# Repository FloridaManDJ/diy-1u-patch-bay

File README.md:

# diy-1u-patch-bay
1U 1/4" audio patch bay

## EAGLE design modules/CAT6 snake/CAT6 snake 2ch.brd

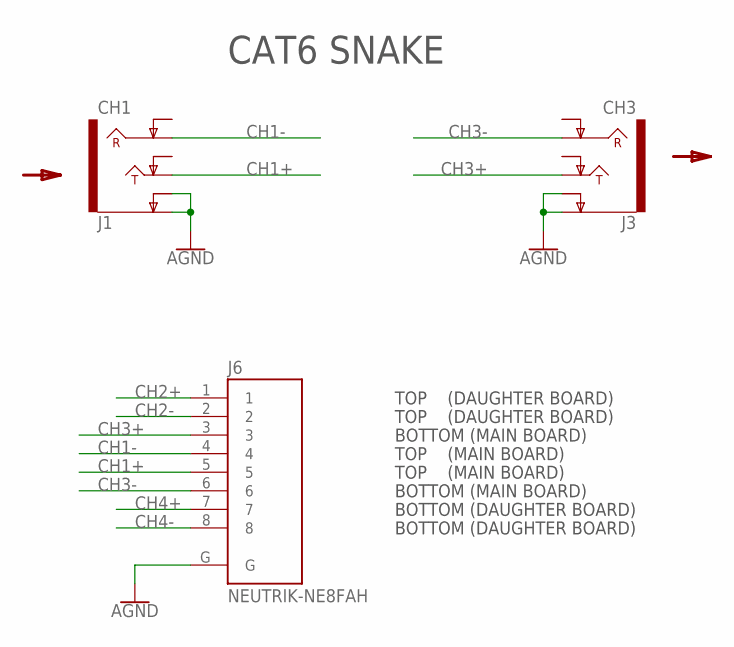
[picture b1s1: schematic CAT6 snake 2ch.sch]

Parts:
J1: CH1; NEUTRIK-NRJ6HF
J3: CH3; NEUTRIK-NRJ6HF
J6: NEUTRIK-NE8FAH; NEUTRIK_NE8FAH

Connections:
AGND: J1.S (EARTH), J1.SN (EARTH-NORM), J3.S (EARTH), J3.SN (EARTH-NORM), J6.G
CH1+: J1.T (TIP), J6.5
CH1-: J1.R (RING), J6.4
CH2+: J6.1
CH2-: J6.2
CH3+: J3.T (TIP), J6.3
CH3-: J3.R (RING), J6.6
CH4+: J6.7
CH4-: J6.8

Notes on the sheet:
TOP (MAIN BOARD)
TOP (DAUGHTER BOARD)
BOTTOM (DAUGHTER BOARD)
BOTTOM (MAIN BOARD)
CAT6 SNAKE

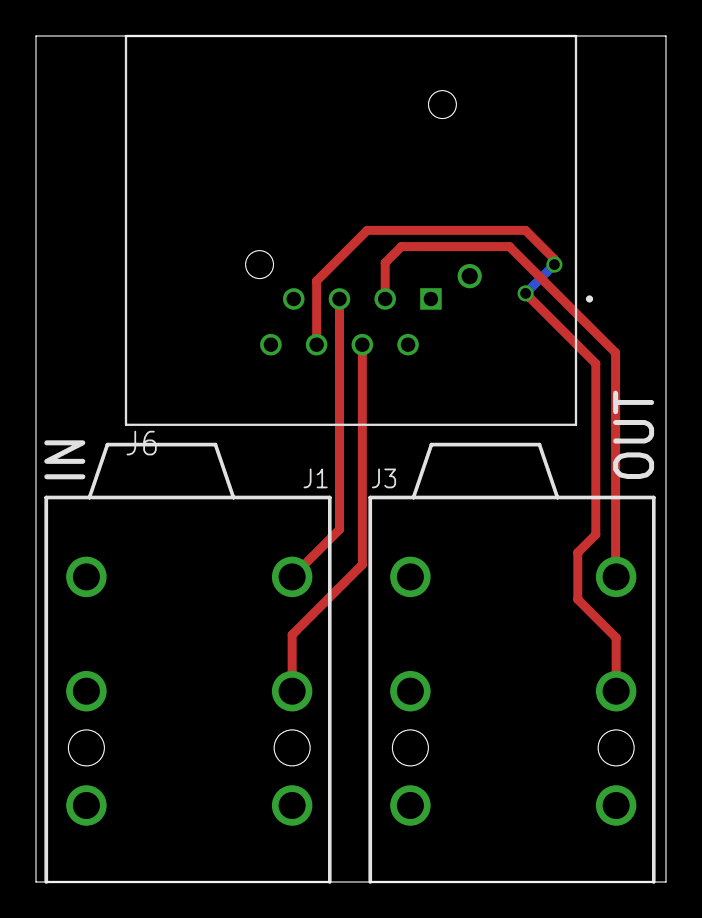
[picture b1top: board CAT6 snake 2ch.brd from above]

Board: 2 copper layers, 35.0 x 47.0 mm, 3 parts (0 on the bottom side), 5 nets.

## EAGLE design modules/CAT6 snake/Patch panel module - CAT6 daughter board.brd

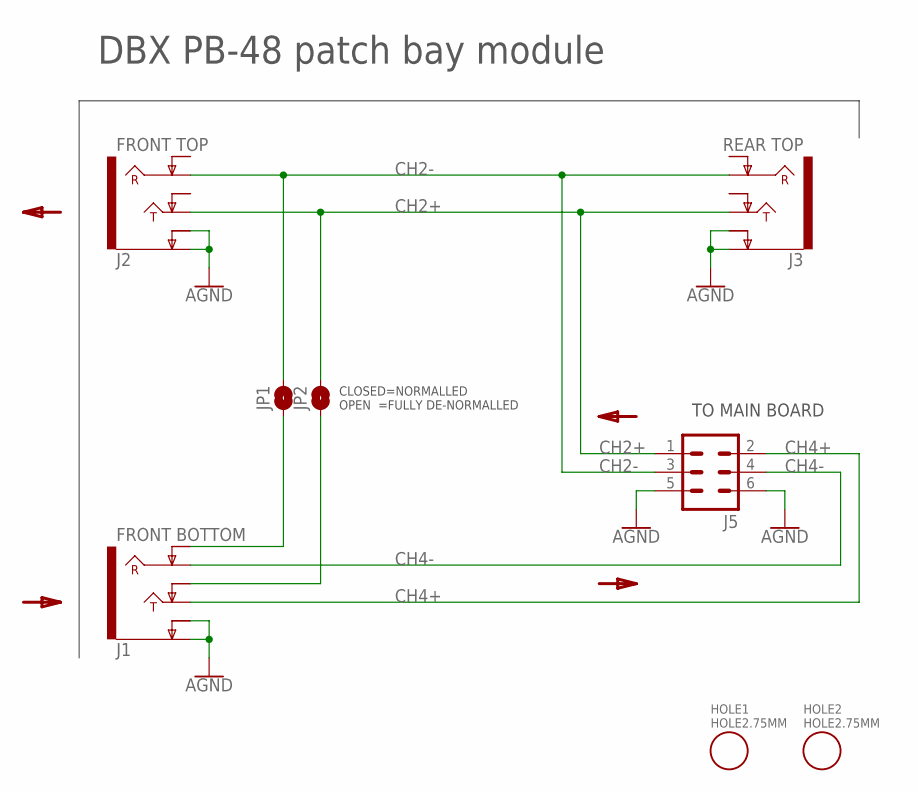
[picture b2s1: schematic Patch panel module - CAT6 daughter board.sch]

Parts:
HOLE1, HOLE2: HOLE2.75MM; HOLE-2.75MM
J1: FRONT BOTTOM; NEUTRIK-NRJ6HF
J2: FRONT TOP; NEUTRIK-NRJ6HF
J3: REAR TOP; NEUTRIK-NRJ6HF
J5: MA03-2
JP1, JP2: JUMPER-SMT_2_NO_NO-SILK_ROUND; SMT-JUMPER_2_NO_NO-SILK_ROUND

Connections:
AGND: J1.S (EARTH), J1.SN (EARTH-NORM), J2.S (EARTH), J2.SN (EARTH-NORM), J3.S (EARTH), J3.SN (EARTH-NORM), J5.5, J5.6
CH2+: J2.T (TIP), J3.T (TIP), J5.1, JP2.2
CH2-: J2.R (RING), J3.R (RING), J5.3, JP1.2
CH4+: J1.T (TIP), J5.2
CH4-: J1.R (RING), J5.4
unnamed: J1.RN (RING-NORM), JP1.1
unnamed: J1.TN (TIP-NORM), JP2.1

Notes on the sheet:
TO MAIN BOARD
CLOSED=NORMALLED OPEN =FULLY DE-NORMALLED
DBX PB-48 patch bay module

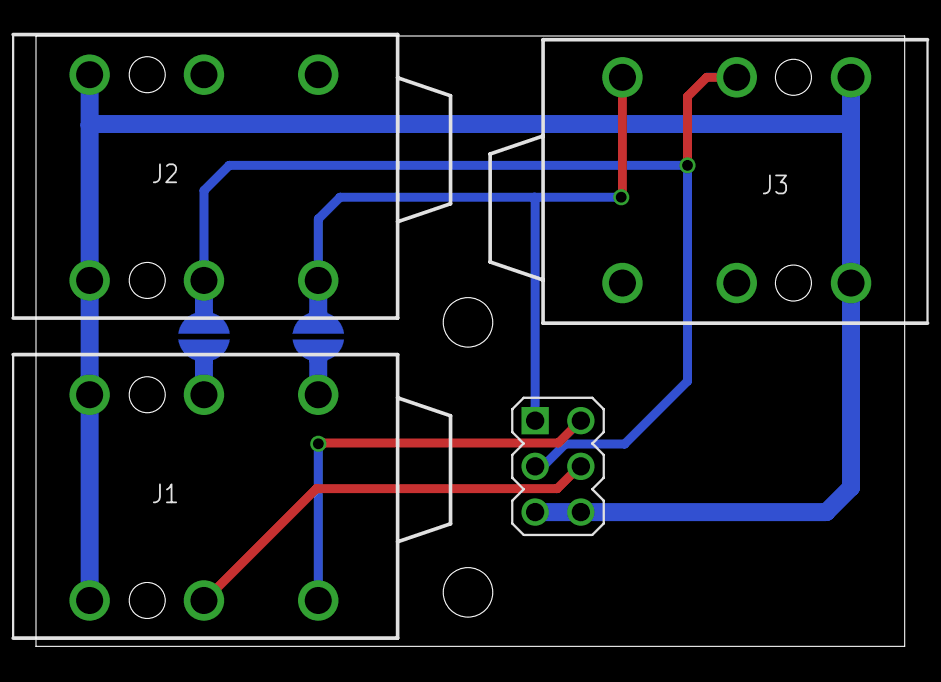
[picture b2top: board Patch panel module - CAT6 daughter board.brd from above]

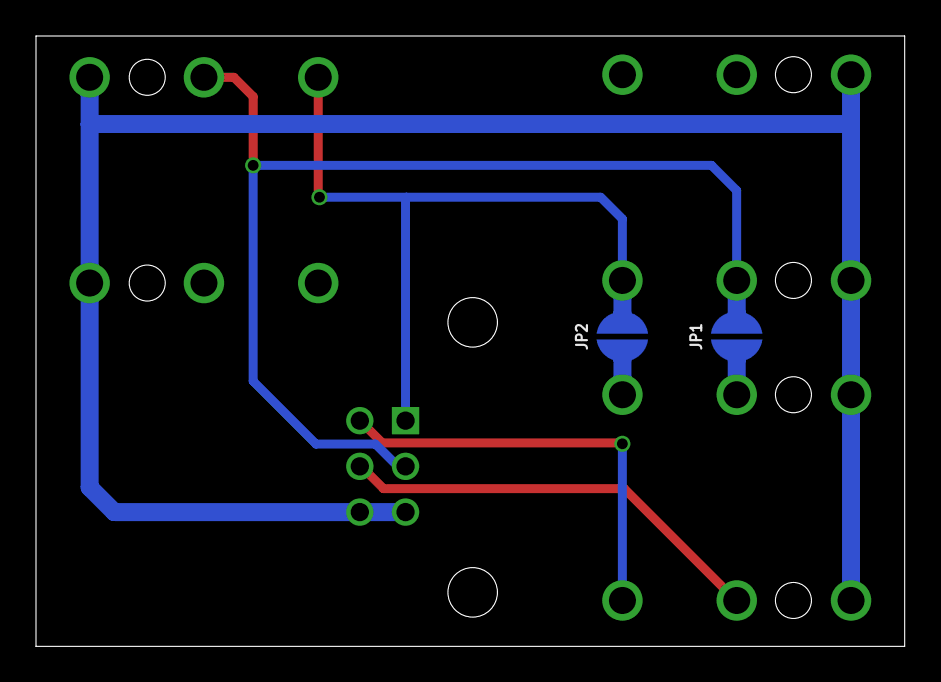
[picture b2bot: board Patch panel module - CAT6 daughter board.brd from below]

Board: 2 copper layers, 48.3 x 33.9 mm, 8 parts (2 on the bottom side), 7 nets.

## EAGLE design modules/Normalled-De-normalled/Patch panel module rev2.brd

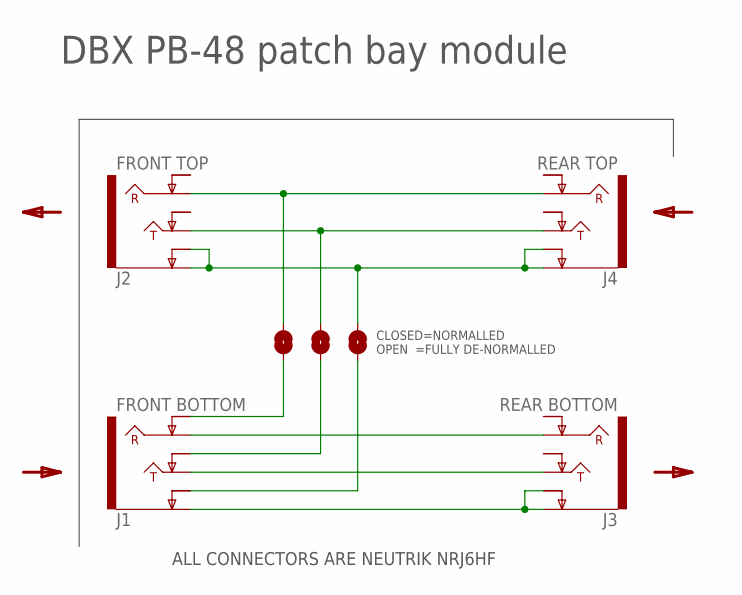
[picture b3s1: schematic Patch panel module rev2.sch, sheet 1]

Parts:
J1: FRONT BOTTOM; NEUTRIK-NRJ6HF
J2: FRONT TOP; NEUTRIK-NRJ6HF
J3: REAR BOTTOM; NEUTRIK-NRJ6HF
J4: REAR TOP; NEUTRIK-NRJ6HF
JP1, JP2, JP3: JUMPER-SMT_2_NO_NO-SILK_ROUND; SMT-JUMPER_2_NO_NO-SILK_ROUND

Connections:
unnamed: J2.S (EARTH), J2.SN (EARTH-NORM), J4.S (EARTH), J4.SN (EARTH-NORM), JP1.1
unnamed: J2.R (RING), J4.R (RING), JP3.1
unnamed: J2.T (TIP), J4.T (TIP), JP2.1
unnamed: J1.R (RING), J3.R (RING)
unnamed: J1.T (TIP), J3.T (TIP)
unnamed: J1.S (EARTH), J3.S (EARTH), J3.SN (EARTH-NORM)
unnamed: J1.SN (EARTH-NORM), JP1.2
unnamed: J1.TN (TIP-NORM), JP2.2
unnamed: J1.RN (RING-NORM), JP3.2

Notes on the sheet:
DBX PB-48 patch bay module
ALL CONNECTORS ARE NEUTRIK NRJ6HF
CLOSED=NORMALLED OPEN =FULLY DE-NORMALLED

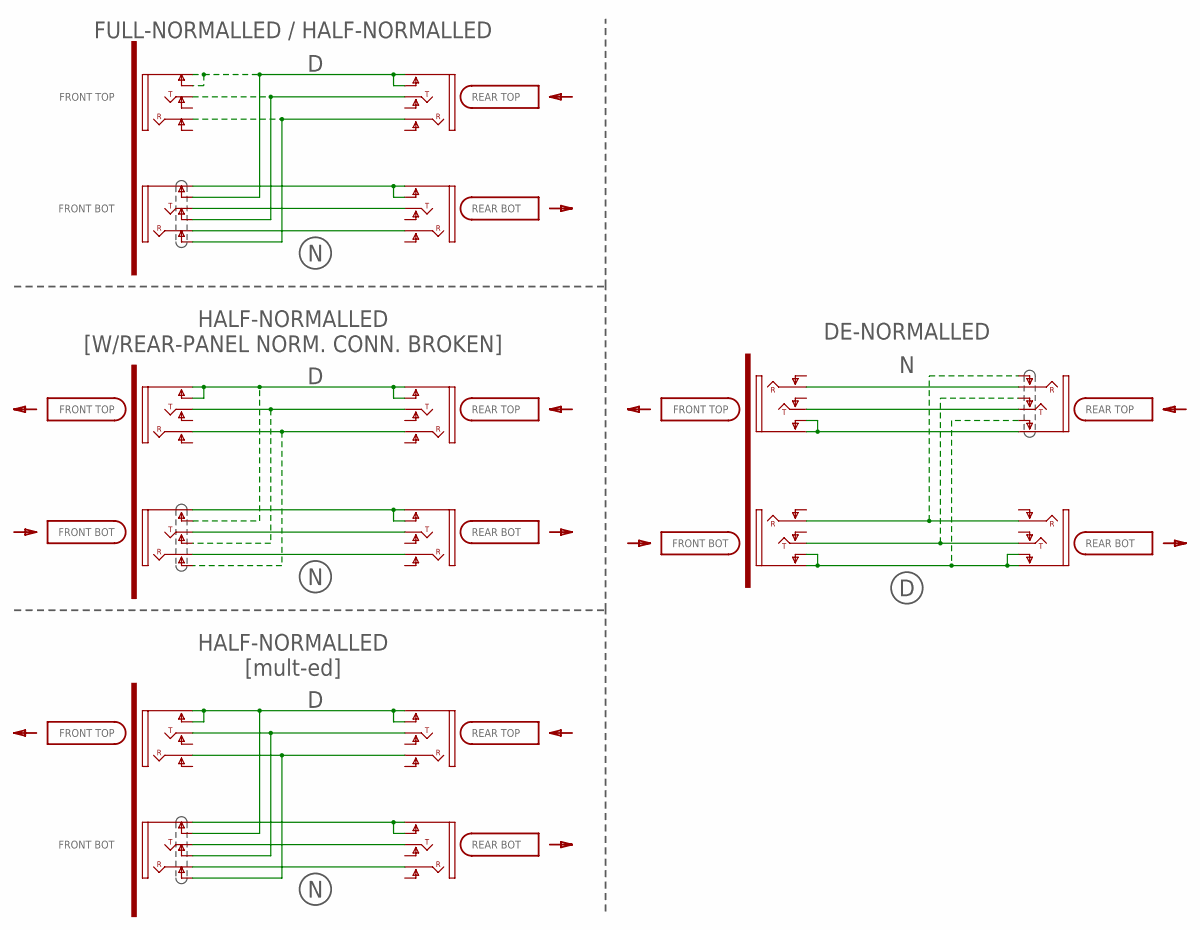
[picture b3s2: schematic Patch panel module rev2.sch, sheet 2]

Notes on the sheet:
FRONT TOP
FRONT BOT
REAR TOP
REAR BOT
FULL-NORMALLED / HALF-NORMALLED
HALF-NORMALLED [W/REAR-PANEL NORM. CONN. BROKEN]
HALF-NORMALLED [mult-ed]
DE-NORMALLED

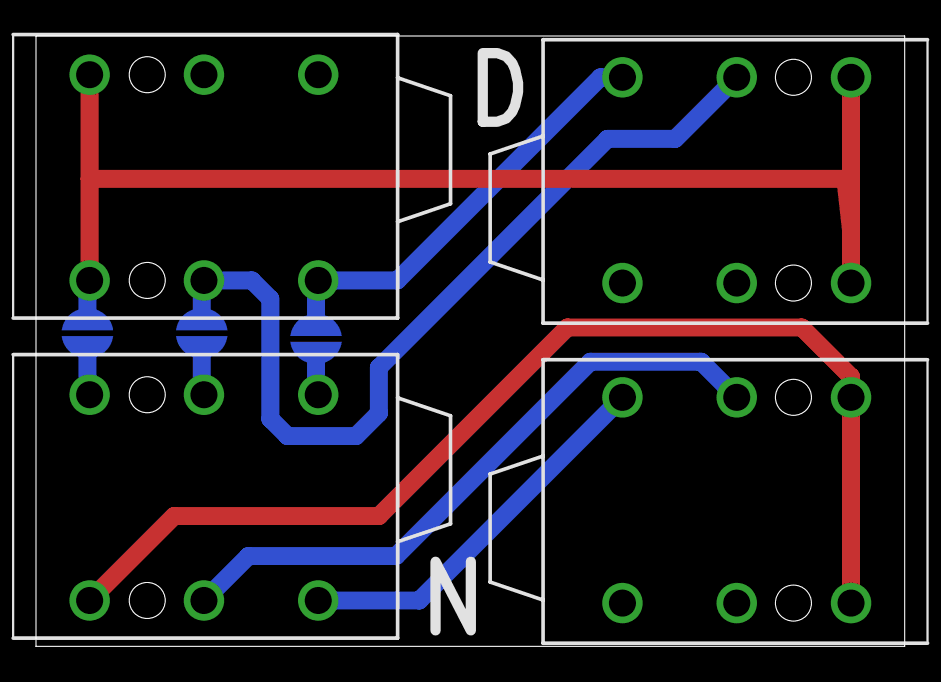
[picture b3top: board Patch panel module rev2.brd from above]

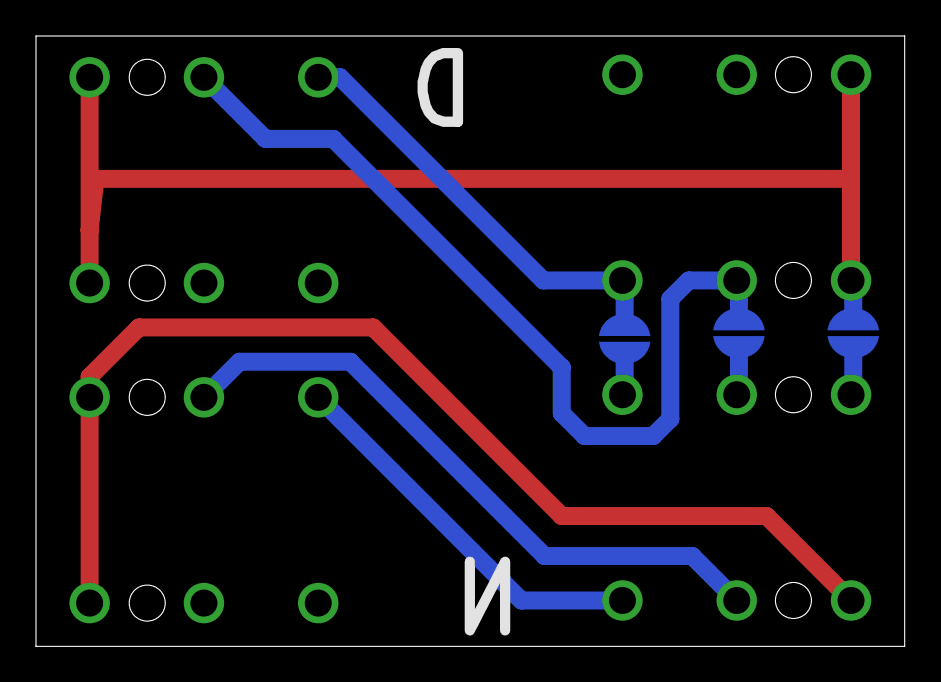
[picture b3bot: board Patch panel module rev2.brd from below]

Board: 2 copper layers, 48.3 x 33.9 mm, 7 parts (3 on the bottom side), 9 nets.

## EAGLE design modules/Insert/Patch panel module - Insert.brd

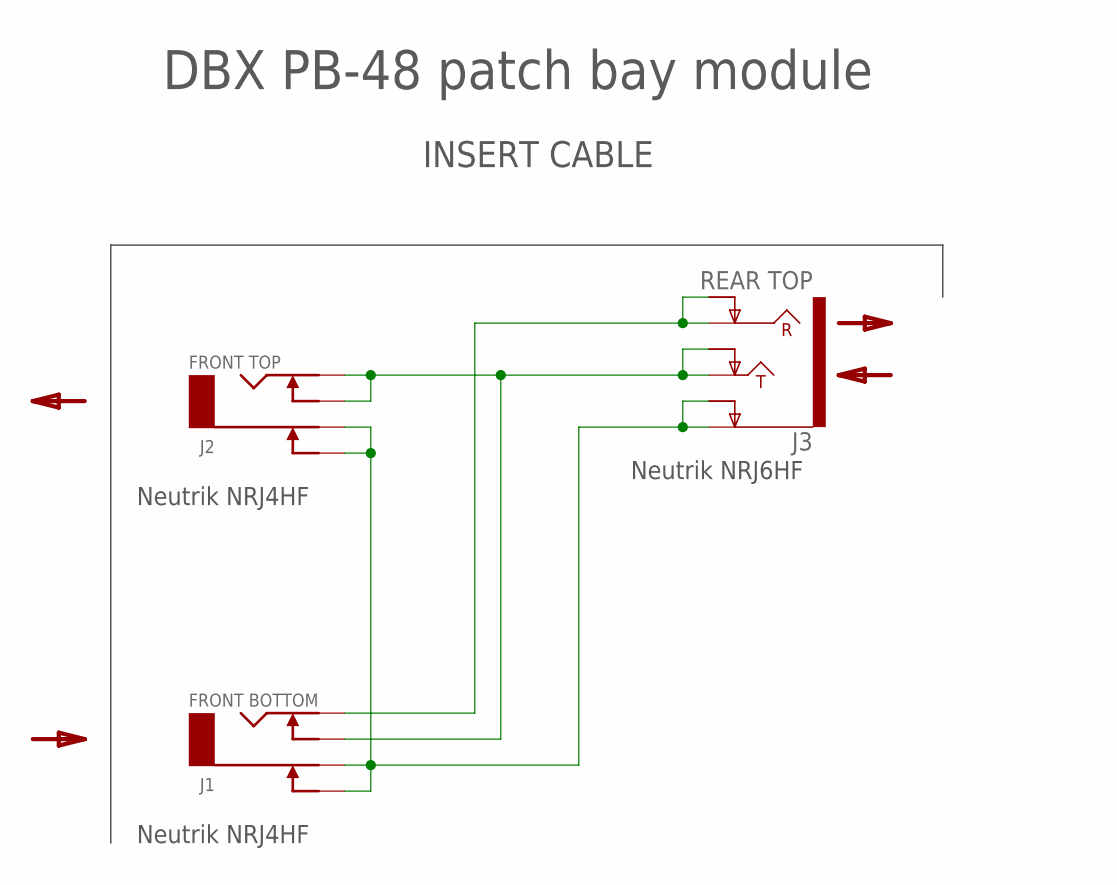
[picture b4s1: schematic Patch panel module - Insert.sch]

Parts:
J1: FRONT BOTTOM; NEUTRIK-NRJ4HF
J2: FRONT TOP; NEUTRIK-NRJ4HF
J3: REAR TOP; NEUTRIK-NRJ6HF

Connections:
unnamed: J1.TN, J2.T (TIP), J2.TN, J3.T (TIP), J3.TN (TIP-NORM)
unnamed: J1.T (TIP), J3.R (RING), J3.RN (RING-NORM)
unnamed: J1.S (SLEEVE), J1.SN, J2.S (SLEEVE), J2.SN, J3.S (EARTH), J3.SN (EARTH-NORM)

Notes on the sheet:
DBX PB-48 patch bay module
Neutrik NRJ6HF
Neutrik NRJ4HF
INSERT CABLE

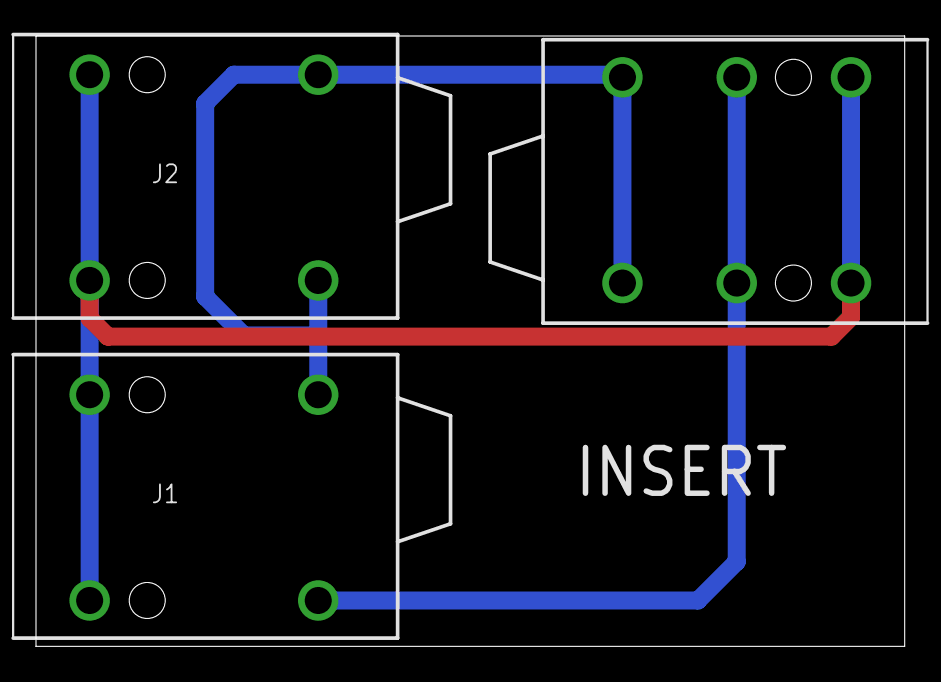
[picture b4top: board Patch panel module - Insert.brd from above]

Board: 2 copper layers, 48.3 x 33.9 mm, 3 parts (0 on the bottom side), 3 nets.

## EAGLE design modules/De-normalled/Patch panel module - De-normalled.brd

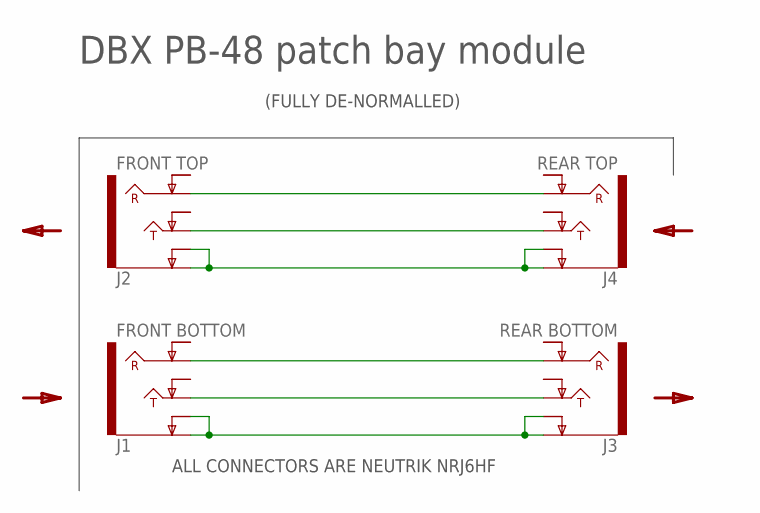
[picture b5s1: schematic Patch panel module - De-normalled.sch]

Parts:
J1: FRONT BOTTOM; NEUTRIK-NRJ6HF
J2: FRONT TOP; NEUTRIK-NRJ6HF
J3: REAR BOTTOM; NEUTRIK-NRJ6HF
J4: REAR TOP; NEUTRIK-NRJ6HF

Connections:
unnamed: J2.S (EARTH), J2.SN (EARTH-NORM), J4.S (EARTH), J4.SN (EARTH-NORM)
unnamed: J2.R (RING), J4.R (RING)
unnamed: J2.T (TIP), J4.T (TIP)
unnamed: J1.R (RING), J3.R (RING)
unnamed: J1.T (TIP), J3.T (TIP)
unnamed: J1.S (EARTH), J1.SN (EARTH-NORM), J3.S (EARTH), J3.SN (EARTH-NORM)

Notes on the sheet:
DBX PB-48 patch bay module
(FULLY DE-NORMALLED)
ALL CONNECTORS ARE NEUTRIK NRJ6HF

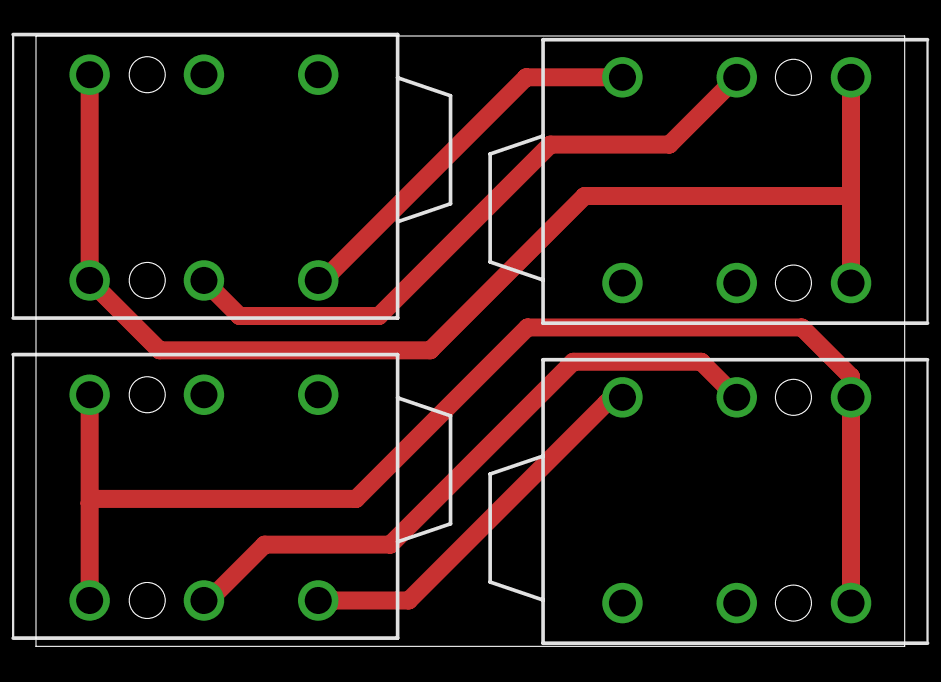
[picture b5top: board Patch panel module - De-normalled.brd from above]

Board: 2 copper layers, 48.3 x 33.9 mm, 4 parts (0 on the bottom side), 6 nets.

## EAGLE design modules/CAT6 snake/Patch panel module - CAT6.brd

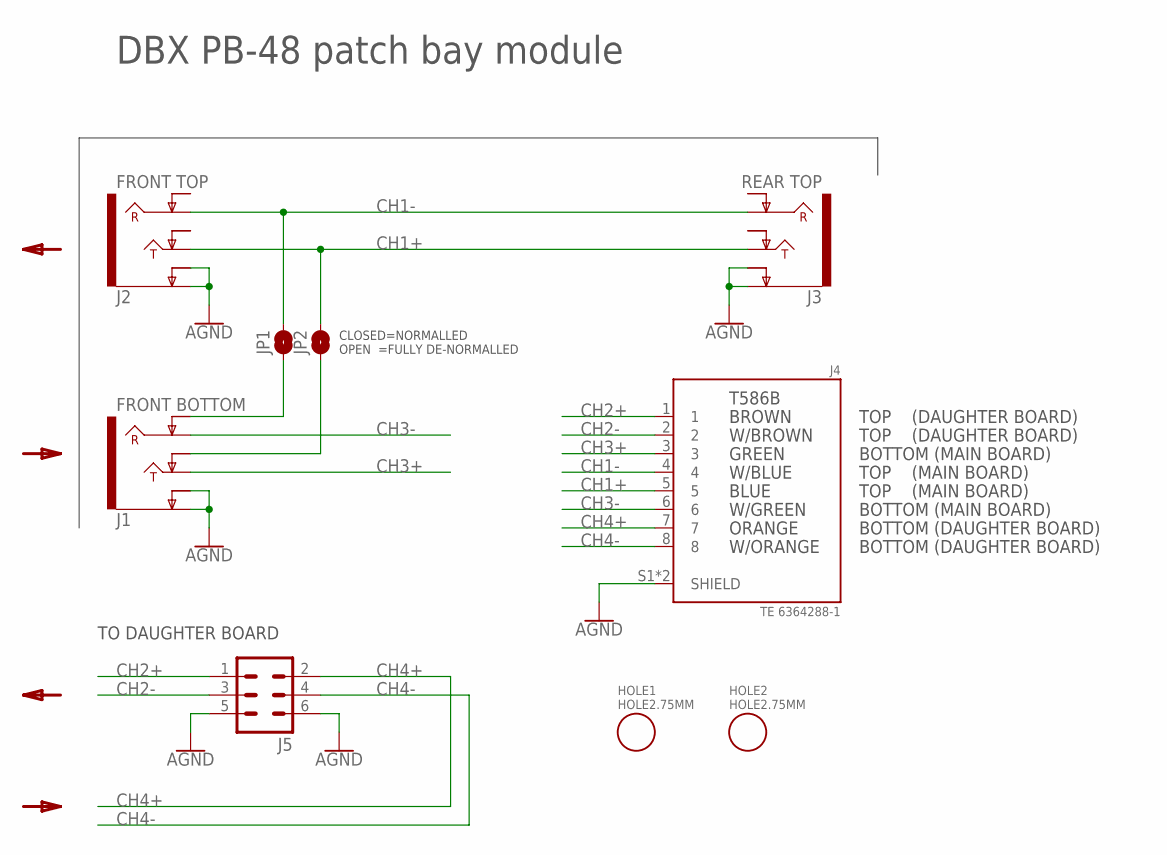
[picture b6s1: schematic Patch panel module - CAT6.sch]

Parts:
HOLE1, HOLE2: HOLE2.75MM; HOLE-2.75MM
J1: FRONT BOTTOM; NEUTRIK-NRJ6HF
J2: FRONT TOP; NEUTRIK-NRJ6HF
J3: REAR TOP; NEUTRIK-NRJ6HF
J4: TE 6364288-1; RJ45-TE-6364288-1
J5: MA03-2
JP1, JP2: JUMPER-SMT_2_NO_NO-SILK_ROUND; SMT-JUMPER_2_NO_NO-SILK_ROUND

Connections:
AGND: J1.S (EARTH), J1.SN (EARTH-NORM), J2.S (EARTH), J2.SN (EARTH-NORM), J3.S (EARTH), J3.SN (EARTH-NORM), J4.S1 (SHIELD), J4.S2 (SHIELD), J5.5, J5.6
CH1+: J2.T (TIP), J3.T (TIP), J4.5, JP2.2
CH1-: J2.R (RING), J3.R (RING), J4.4, JP1.2
CH2+: J4.1, J5.1
CH2-: J4.2, J5.3
CH3+: J1.T (TIP), J4.3
CH3-: J1.R (RING), J4.6
CH4+: J4.7, J5.2
CH4-: J4.8, J5.4
unnamed: J1.RN (RING-NORM), JP1.1
unnamed: J1.TN (TIP-NORM), JP2.1

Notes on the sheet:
TO DAUGHTER BOARD
TOP (MAIN BOARD)
TOP (DAUGHTER BOARD)
BOTTOM (DAUGHTER BOARD)
BOTTOM (MAIN BOARD)
CLOSED=NORMALLED OPEN =FULLY DE-NORMALLED
DBX PB-48 patch bay module

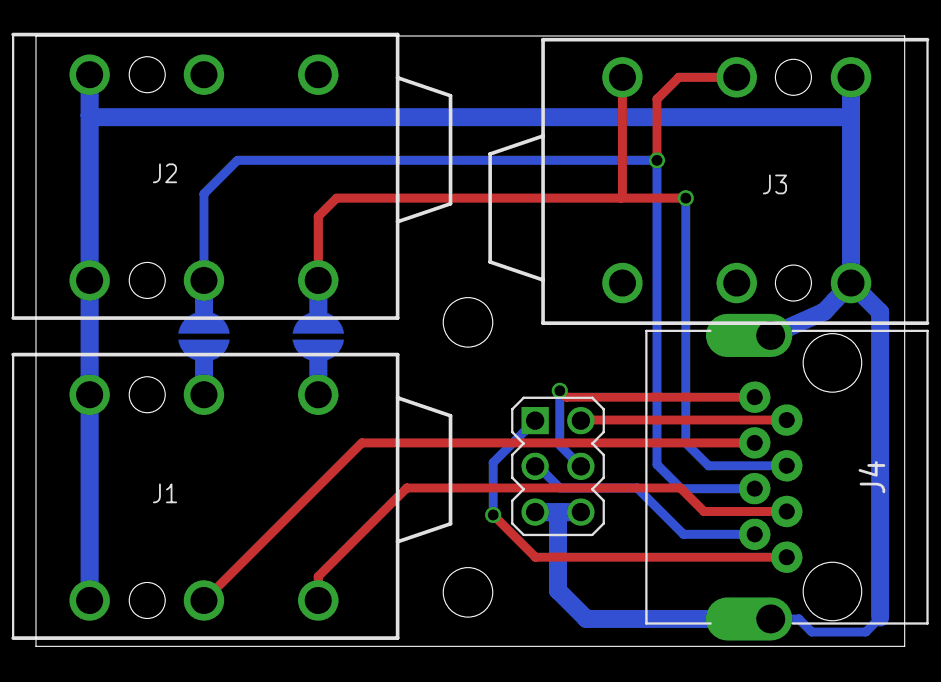
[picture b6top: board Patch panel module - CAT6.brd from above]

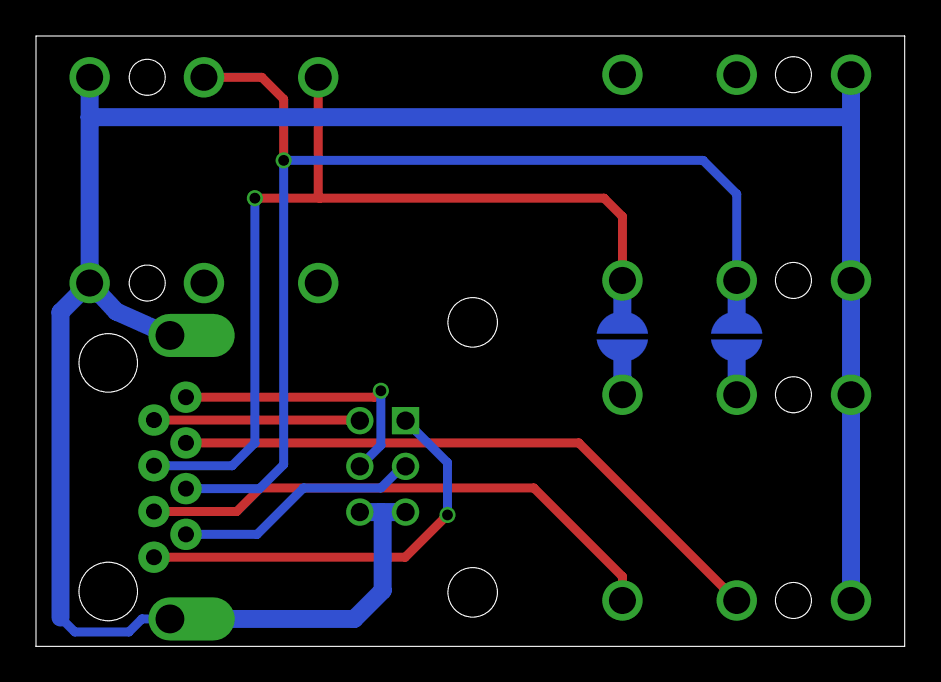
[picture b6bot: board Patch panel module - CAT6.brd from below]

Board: 2 copper layers, 48.3 x 33.9 mm, 9 parts (2 on the bottom side), 11 nets.

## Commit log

2026-05-21 add pictures
2026-05-21 add Alibre CAD files
2026-05-21 Add datasheets
2026-05-21 add gerber files
2026-05-21 Add eagle sch/pcb files
2026-05-21 add patch panel sheet metal cut file
